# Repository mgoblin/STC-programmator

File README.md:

# STC programmator to upload hex firmare to MCU flash.

This repo contains kicad electrical scheme, pcb design and description of STC programmator.

STC is a family of microcontrollers with 8051 architecture.

The electrical scheme and PCB design are a Kicad files. 

# Table of contents
* [Programmator usage](https://github.com/mgoblin/STC-programmator/tree/main?tab=readme-ov-file#programmator-usage)
  * [How to connect programmator](https://github.com/mgoblin/STC-programmator/tree/main#how-to-connect-programmator)
  * [Upload firmare from Platfromio to MCU](https://github.com/mgoblin/STC-programmator#upload-firmare-from-platfromio-to-mcu)
* [Electrical sheme](https://github.com/mgoblin/STC-programmator/tree/main?tab=readme-ov-file#electrical-sheme)
  * [TxD-RxD part](https://github.com/mgoblin/STC-programmator/blob/main/README.md#txd-rxd-part)
  * [VCC part](https://github.com/mgoblin/STC-programmator#vcc-part)
* [PCB design](https://github.com/mgoblin/STC-programmator/tree/main?tab=readme-ov-file#pcb-design)
* [Alternative path](https://github.com/mgoblin/STC-programmator/blob/main/README.md#alternative-path)

# Programmator usage
Programmator used with USB-2-TTL adapter. 

CHG340g is a popular USB-2-TTL adapter.

CHG340g should be connected to PC USB port and programmator is placed between CGH340g and STC MCU. 

## How to connect programmator
J1 for USB adapter
 - J1 +5V pin should be connected to USB adapter +5V pin.
 - J1 GND pin should be connected to USB adapter GND pin.
 - J1 TxD pin should be connected to USB adapter TxD pin.
 - J1 RxD pin should be connected to USB adapter RxD pin.

J2 for MCU 
 - J2 +5V pin should be connected to MCU +5V pin.
 - J2 GND pin should be connected to MCU GND pin.
 - J2 TxD pin should be connected to MCU TxD pin.
 - J2 RxD pin should be connected to MCU RxD pin.

   Jumper J1 is opened.

**Inside programmator USB TxD is routed to MCU RxD and USB RxD is routed to MCU TxD pin.**

## Upload firmare from Platfromio to MCU
[Plaformio] (https://platformio.org/) is a popular embedded software development IDE based on [Visual Studio Code](https://code.visualstudio.com/).

Platfromio use [stcgal](https://github.com/grigorig/stcgal/) to upload firmware. 

Jumper J1 should be opened before uploading start. 

1. Connect USB adapter with programmator (see [How to connect programmator section](#How-to-connect-programmator)). JP1 jumper should be opened.
2. Connect programmator to MCU pins. Developer boards and many PCB designs have dedicated pins.
3. Run Platfromio and open your STC project with source code that will be compiled to firmware.
4. Connect USB adapter to PC.
5. In Platfromio start upload. The most popular way to do this is press upload button
6. Platformio open terminal panel and output upload status as a messages to it
7. Waiting for "Cycling power: done" message. Uploading process waiting.
   > Cycling power: done
8. Press and hold the SW1 button on the programmer until the download process is complete.
    
9. Uploading proccess completes with messages
>Finishing write: done
>
>Setting options: done
>
>Target UID: <MCU chipid here>

>Disconnected!
>
10. You can release the button or hold it if you want to see how the downloaded firmware works.
11. For permanently firmware execution close J1 jumper

# Electrical sheme

Scheme contains two important parts: TxD-RxD part and VCC part.

## TxD-RxD part
The principle of connection between MCU and USB adapter is RxD <-> TxD.
R1 and D1 are used to eliminate parasitic power supply through the pins to the microcontroller. 

## VCC part
The MCU is powered via USB-2-TTL adapter. MCU GND connect to USB adapter GND.
USB adapter +5V connected to button SW1 and jumper JP1.

If the jumper JP1 is shorted, the microcontroller runs the loaded firmware and cannot be programmed.
In firmware download mode, the jumper is open and power is supplied only when the SW1 button is pressed and held.

Capacitors C1-C3 debounce of the SW1 button. In the classic programmator scheme only one 47mF polaraized capacitor is placed. 
But i have only 100mF capasitors and connect it in a chain to get 50mF capacity.    

# PCB design

# Alternative path 
You can upload firmware to STC MCU with USB-To-TTL adapter only.

For this way disconnect GND wire from MCU and start firware upload.
When stcgal out will be "Cycling power: done" connect GND from adapter to MCU.

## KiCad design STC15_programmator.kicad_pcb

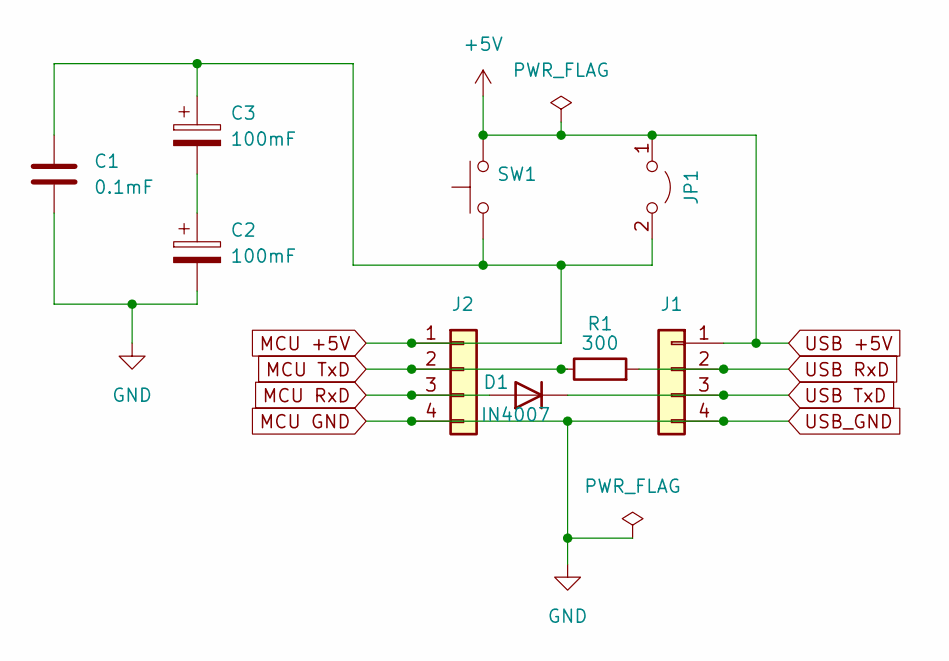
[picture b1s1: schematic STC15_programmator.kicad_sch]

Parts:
C1: 0.1mF; C_Disc_D3.0mm_W2.0mm_P2.50mm
C2, C3: 100mF; CP_Radial_D5.0mm_P2.50mm
D1: IN4007; D_DO-41_SOD81_P12.70mm_Horizontal
J1, J2: Conn_01x04; PinHeader_1x04_P2.54mm_Vertical
JP1: Jumper_2_Open; PinHeader_2x01_P2.54mm_Vertical
R1: 300; R_Axial_DIN0309_L9.0mm_D3.2mm_P12.70mm_Horizontal
SW1: SW_Push; SW_PUSH-12mm

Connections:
MCU +5V: C1.1, C3.1, J2.1, JP1.2 (B), SW1.1
MCU GND: C1.2, C2.2, J1.4, J2.4
MCU RxD: D1.2 (A), J2.3
MCU TxD: J2.2, R1.1
unnamed: C2.1, C3.2
USB +5V: J1.1, JP1.1 (A), SW1.2
USB RxD: J1.2, R1.2
USB TxD: D1.1 (K), J1.3

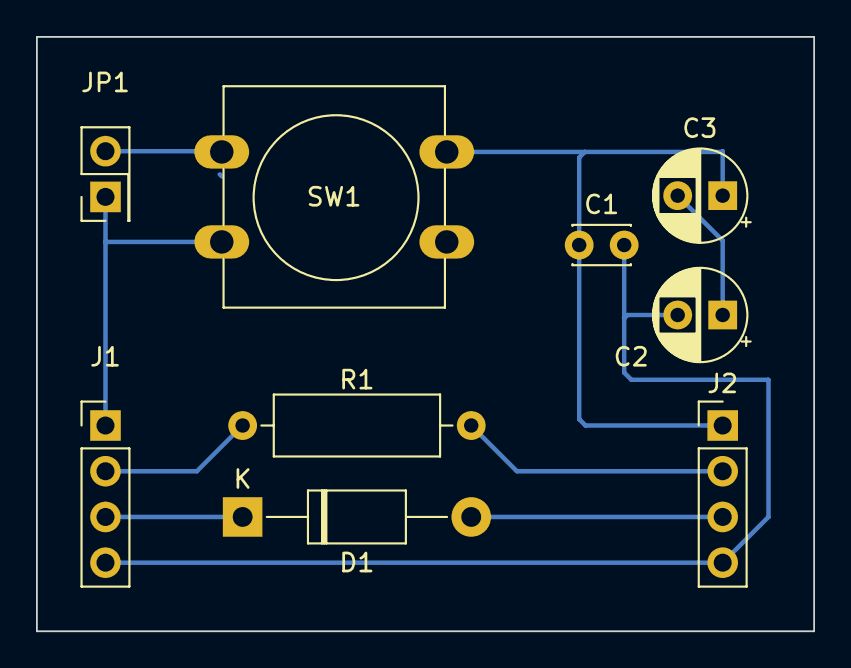
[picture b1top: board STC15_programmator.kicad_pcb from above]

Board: 2 copper layers, 43.2 x 33.0 mm, 9 parts (0 on the bottom side), 8 nets.

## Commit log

2024-12-08 add images
2024-12-08 Add view image
2024-12-08 Optimize image size
